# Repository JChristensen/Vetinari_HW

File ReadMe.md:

#ATtiny84A Vetinari Clock Driver Schematic and PC Board Layout

####CC BY-SA
ATtiny84A Vetinari Clock Driver by Jack Christensen is licensed under
the Creative Commons Attribution-ShareAlike 3.0 Unported License.
To view a copy of this license, visit //http://creativecommons.org/licenses/by-sa/3.0/
or send a letter to Creative Commons, 171 Second Street, Suite 300,
San Francisco, California, 94105, USA.

Hardware: http://goo.gl/Rsk2Ki  
Software: http://goo.gl/oXYS8Y

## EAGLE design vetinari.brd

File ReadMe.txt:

ATtiny84A Vetinari Clock Driver Schematic and PC Board Layout

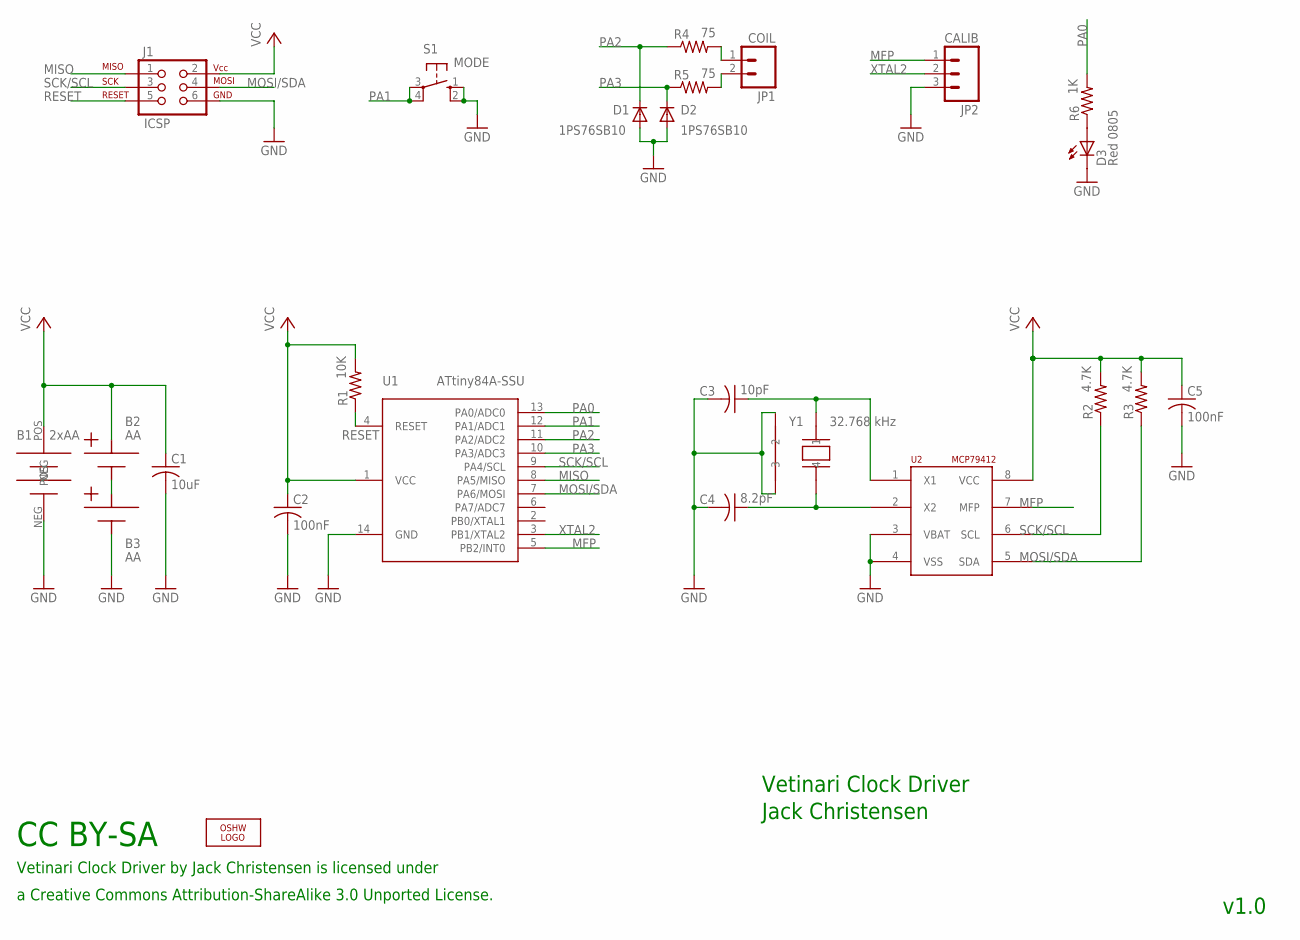
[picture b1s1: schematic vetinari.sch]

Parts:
B1: 2xAA; KEYSTONE-2462-OUTLINE
B2, B3: AA; BATT-AA-PC-CLIPS
C1: 10uF; M1206
C2, C5: 100nF; M0805
C3: 10pF; M0805
C4: 8.2pF; M0805
D1: 1PS76SB10; SOD-323F
D2: 1PS76SB10; SOD-323F-A
D3: Red 0805; D0805
J1: ICSP; 2X3_LOCK
JP1: COIL; 1X02
JP2: CALIB; 1X03_LOCK
LOGO2: OSHW_LOGO_8MILX0150-NT; OSHW_8X150_NOTEXT
R1: 10K; M0805
R2, R3: 4.7K; M0805
R4, R5: 75; M0805
R6: 1K; M0805
S1: MODE; B3F-10XXOCT
U1: ATtiny84A-SSU; SO14
U2: MCP79412; SO08
Y1: 32.768 kHz; CRYSTAL-CITIZEN-CM2XXC

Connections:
GND: B1.NEG, B3.N1, B3.N2, C1.2, C2.2, C3.2, C4.2, C5.2, D1.A, D2.A, D3.K (C), J1.6, JP2.3, S1.1 (S), S1.2 (S1), U1.14 (GND), U2.3 (VBAT), U2.4 (VSS), Y1.P$2 (2), Y1.P$3 (3)
MFP: JP2.1, U1.5 (PB2/INT0), U2.7 (MFP)
MISO: J1.1, U1.8 (PA5/MISO)
MOSI/SDA: J1.4, R3.1, U1.7 (PA6/MOSI), U2.5 (SDA)
unnamed: JP1.1, R4.2
unnamed: C4.1, U2.2 (X2), Y1.P$4 (4)
unnamed: C3.1, U2.1 (X1), Y1.P$1 (1)
unnamed: JP1.2, R5.2
unnamed: D3.A, R6.1
unnamed: B2.N1, B2.N2, B3.P1, B3.P2
PA0: R6.2, U1.13 (PA0/ADC0)
PA1: S1.3, S1.4 (P1), U1.12 (PA1/ADC1)
PA2: D1.K, R4.1, U1.11 (PA2/ADC2)
PA3: D2.K, R5.1, U1.10 (PA3/ADC3)
RESET: J1.5, R1.1, U1.4 (RESET)
SCK/SCL: J1.3, R2.1, U1.9 (PA4/SCL), U2.6 (SCL)
VCC: B1.POS, B2.P1, B2.P2, C1.1, C2.1, C5.1, J1.2, R1.2, R2.2, R3.2, U1.1 (VCC), U2.8 (VCC)
XTAL2: JP2.2, U1.3 (PB1/XTAL2)

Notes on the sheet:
Vetinari Clock Driver by Jack Christensen is licensed under
CC BY-SA
a Creative Commons Attribution-ShareAlike 3.0 Unported License.
Vetinari Clock Driver
Jack Christensen
v1.0

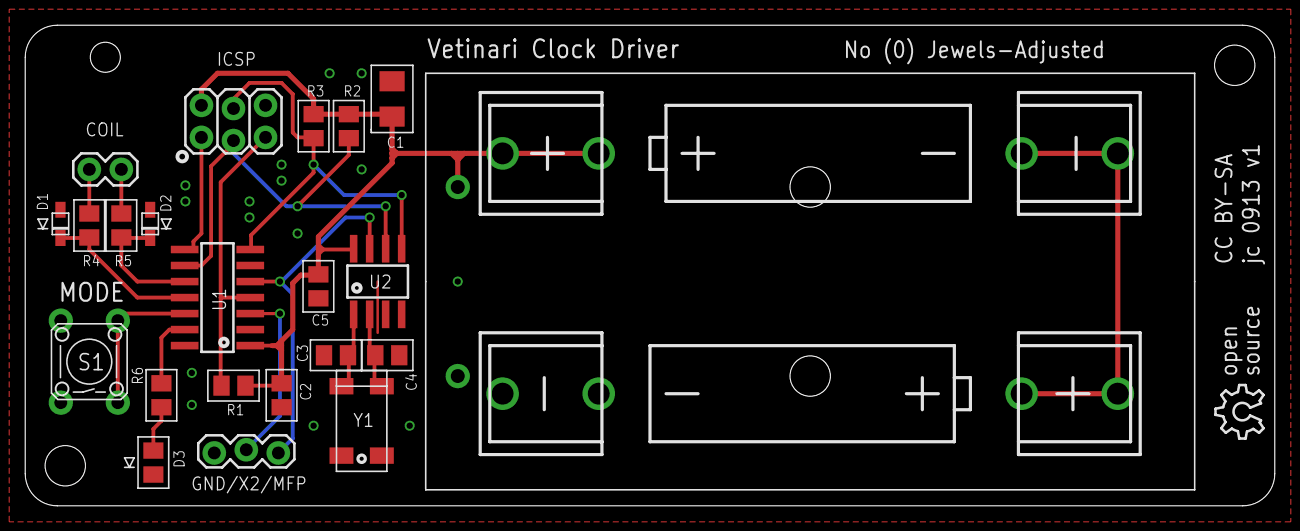
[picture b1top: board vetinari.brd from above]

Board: 2 copper layers, 99.1 x 38.1 mm, 26 parts (1 on the bottom side), 18 nets.

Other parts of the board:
U$1: OSHW_FILLX200_NOTEXT

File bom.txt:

Partlist exported from C:/Users/Jack/Documents/eagle/projects/vetinari/vetinari.sch at 10/23/2013 12:25:12 PM

Part  Value                  Device                 Package                Description                
B1    2xAA                   BATTERY-2AAOUTLINE     KEYSTONE-2462-OUTLINE                             
B2    AA                     BATTERY-AAKEYSTONE-92  BATT-AA-PC-CLIPS                                  
B3    AA                     BATTERY-AAKEYSTONE-92  BATT-AA-PC-CLIPS                                  
C1    10uF                   C-USM1206              M1206                  CAPACITOR, American symbol 
C2    100nF                  C-USM0805              M0805                  CAPACITOR, American symbol 
C3    10pF                   C-USM0805              M0805                  CAPACITOR, American symbol 
C4    8.2pF                  C-USM0805              M0805                  CAPACITOR, American symbol 
C5    100nF                  C-USM0805              M0805                  CAPACITOR, American symbol 
D1    1PS76SB10              DIODESOD-323F          SOD-323F                                          
D2    1PS76SB10              DIODESOD-323F-A        SOD-323F-A                                        
D3    Red 0805               LEDD0805               D0805                  LED                        
J1    ICSP                   AVR_SPI_PRG_62X3_LOCK  2X3_LOCK               AVR ISP 6 Pin              
JP1   COIL                   M02PTH                 1X02                   Header 2                   
JP2   CALIB                  M03LOCK                1X03_LOCK              Header 3                   
LOGO2 OSHW_LOGO_8MILX0150-NT OSHW_LOGO_8MILX0150-NT OSHW_8X150_NOTEXT                                 
R1    10K                    R-US_M0805             M0805                  RESISTOR, American symbol  
R2    4.7K                   R-US_M0805             M0805                  RESISTOR, American symbol  
R3    4.7K                   R-US_M0805             M0805                  RESISTOR, American symbol  
R4    75                     R-US_M0805             M0805                  RESISTOR, American symbol  
R5    75                     R-US_M0805             M0805                  RESISTOR, American symbol  
R6    1K                     R-US_M0805             M0805                  RESISTOR, American symbol  
S1    MODE                   10-XXOCT               B3F-10XXOCT            OMRON SWITCH               
U1    ATtiny84A-SSU          ATTINYX4SO14           SO14                                              
U2    MCP79412               MCP7941X-SOIC-8        SO08                                              
Y1    32.768 kHz             CRYSTAL-CITIZEN-CM2XXC CRYSTAL-CITIZEN-CM2XXC

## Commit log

2013-09-29 v1 as sent to fab
2013-10-27 Tweak trace on board, add .txt doc files and .png images.
2013-11-08 Update ReadMe, LICENSE files.

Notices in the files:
vetinari.brd:
CC BY-SA jc 0913 v1
parts and their libraries:
SparkFun: Licensing: CC v3.0 Share-Alike You are welcome to use this library for commercial purposes.
